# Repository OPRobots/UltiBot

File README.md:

# UltiBot

Robot de Minisumo con 6 sensores SHARP GP2Y0E03

<table>
<tr>
<td  colspan="2">  </td>
</tr>
<tr>
<td>  </td>
<td>  </td>
</tr>
</table>

## Hardware
- STM32F401CCU6 (Principal) Y STM32F103C8T6 (FOC)
- 2x SimleFOCMini
- 2x Motores gimbal 12v 80T
- 2xLiPo 3S ~180 mAh
- 6x Sensores SHARP GP2Y0E03
- 2x Sensores QRE1113
- Ruedas JSUMO JS2622
- Chasis impreso en PLA

## Software
- Programado con VSCode y PlatformIO
- Disponible programa con estrategias básicas

## KiCAD

### PCB UltiBot v1.0

### Librerías

Las librerías necesarias para este proyecto se encuentran en [OPRobots/KiCADLibraries](https://github.com/OPRobots/KiCADLibraries)

La estructura tiene que quedar de la siguiente forma:

```bash
└── kicad_project
    └── custom_libraries
        ├── custom_footprints
        │   ├── *.kicad_mod
        │   └── ...
        └── custom_symbols.kicad_sym
```

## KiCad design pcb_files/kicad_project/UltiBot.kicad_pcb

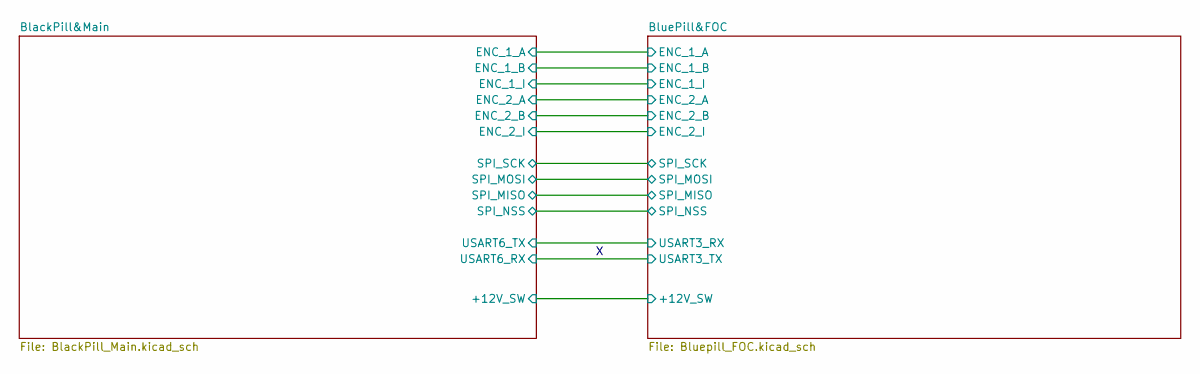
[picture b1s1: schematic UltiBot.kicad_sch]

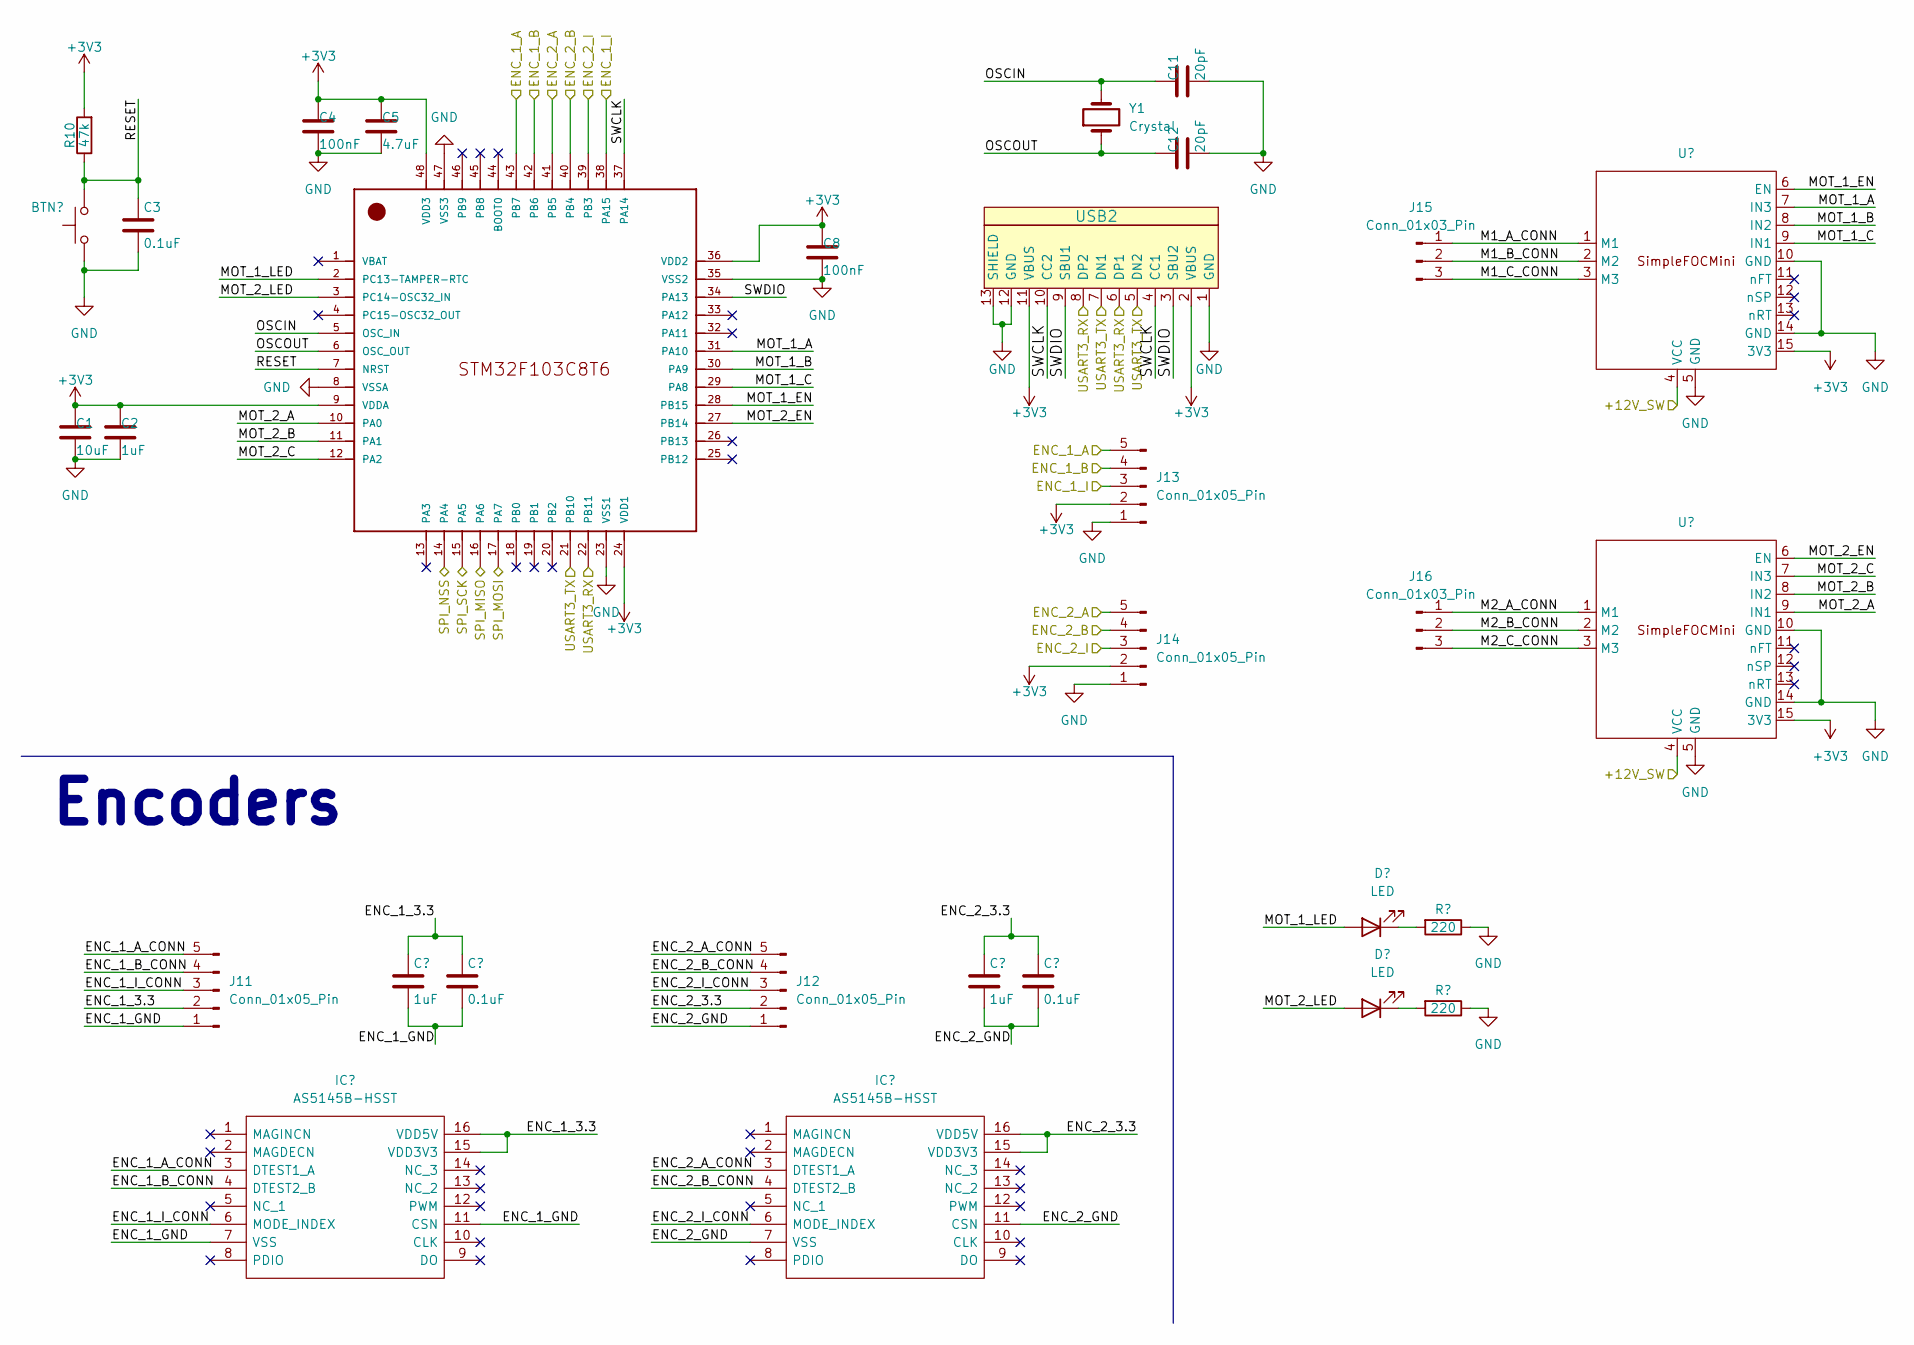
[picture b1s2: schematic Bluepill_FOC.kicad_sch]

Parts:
BTN3: SW_SPST_EVQPE1
C1: 10uF; C_0805_2012Metric
C2, C6, C9: 1uF; C_0805_2012Metric
C3, C7, C10: 0.1uF; C_0805_2012Metric
C4, C8: 100nF; C_0805_2012Metric
C5: 4.7uF; C_0805_2012Metric
C11, C12: 20pF; C_0805_2012Metric
D8, D9: LED; LED_0805_2012Metric
IC1, IC2: AS5145B-HSST; SSOP-16_5.3x6.2mm_P0.65mm
J11, J12, J13, J14: Conn_01x05_Pin; 1x05 Pad
J15, J16: Conn_01x03_Pin; PinHeader_1x03_P2.54mm_Vertical
R10: 47k; R_0805_2012Metric
R11, R12: 220; R_0805_2012Metric_Pad1.20x1.40mm_HandSolder
U2: BluePill; LQFP-48_7x7mm_P0.5mm
U3, U4: SimpleFOCMini
USB2: USB-C ST-Link USART
Y1: Crystal; Crystal_SMD_5032-2Pin_5.0x3.2mm

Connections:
+3V3: C1.1, C2.1, C4.1, C5.1, C8.1, J13.2, J14.2, R10.2, U2.9 (VDDA), U2.24 (VDD1), U2.36 (VDD2), U2.48 (VDD3), U3.15 (3V3), U4.15 (3V3), USB2.2 (VBUS), USB2.11 (VBUS); also elsewhere on the board
/BlackPill&Main/+12V_SW: U3.4 (VCC), U4.4 (VCC); also elsewhere on the board
/BlackPill&Main/ENC_1_A: J13.5, U2.43 (PB7); also elsewhere on the board
/BlackPill&Main/ENC_1_B: J13.4, U2.42 (PB6); also elsewhere on the board
/BlackPill&Main/ENC_1_I: J13.3, U2.38 (PA15); also elsewhere on the board
/BlackPill&Main/ENC_2_A: J14.5, U2.41 (PB5); also elsewhere on the board
/BlackPill&Main/ENC_2_B: J14.4, U2.40 (PB4); also elsewhere on the board
/BlackPill&Main/ENC_2_I: J14.3, U2.39 (PB3); also elsewhere on the board
/BlackPill&Main/SPI_MISO: U2.16 (PA6); also elsewhere on the board
/BlackPill&Main/SPI_MOSI: U2.17 (PA7); also elsewhere on the board
/BlackPill&Main/SPI_NSS: U2.14 (PA4); also elsewhere on the board
/BlackPill&Main/SPI_SCK: U2.15 (PA5); also elsewhere on the board
/BlackPill&Main/USART6_RX: U2.21 (PB10), USB2.5 (DN2), USB2.7 (DN1); also elsewhere on the board
/BlackPill&Main/USART6_TX: U2.22 (PB11), USB2.6 (DP1), USB2.8 (DP2); also elsewhere on the board
/BluePill&FOC/ENC_1_3.3: C6.1, C7.1, IC1.15 (VDD3V3), IC1.16 (VDD5V), J11.2
/BluePill&FOC/ENC_1_A_CONN: IC1.3 (DTEST1_A), J11.5
/BluePill&FOC/ENC_1_B_CONN: IC1.4 (DTEST2_B), J11.4
/BluePill&FOC/ENC_1_GND: C6.2, C7.2, IC1.7 (VSS), IC1.11 (CSN), J11.1
/BluePill&FOC/ENC_1_I_CONN: IC1.6 (MODE_INDEX), J11.3
/BluePill&FOC/ENC_2_3.3: C9.1, C10.1, IC2.15 (VDD3V3), IC2.16 (VDD5V), J12.2
/BluePill&FOC/ENC_2_A_CONN: IC2.3 (DTEST1_A), J12.5
/BluePill&FOC/ENC_2_B_CONN: IC2.4 (DTEST2_B), J12.4
/BluePill&FOC/ENC_2_GND: C9.2, C10.2, IC2.7 (VSS), IC2.11 (CSN), J12.1
/BluePill&FOC/ENC_2_I_CONN: IC2.6 (MODE_INDEX), J12.3
/BluePill&FOC/M1_A_CONN: J15.1, U3.1 (M1)
/BluePill&FOC/M1_B_CONN: J15.2, U3.2 (M2)
/BluePill&FOC/M1_C_CONN: J15.3, U3.3 (M3)
/BluePill&FOC/M2_A_CONN: J16.1, U4.1 (M1)
/BluePill&FOC/M2_B_CONN: J16.2, U4.2 (M2)
/BluePill&FOC/M2_C_CONN: J16.3, U4.3 (M3)
/BluePill&FOC/MOT_1_A: U2.31 (PA10), U3.7 (IN3)
/BluePill&FOC/MOT_1_B: U2.30 (PA9), U3.8 (IN2)
/BluePill&FOC/MOT_1_C: U2.29 (PA8), U3.9 (IN1)
/BluePill&FOC/MOT_1_EN: U2.28 (PB15), U3.6 (EN)
/BluePill&FOC/MOT_1_LED: D8.2 (A), U2.2 (PC13-TAMPER-RTC)
/BluePill&FOC/MOT_2_A: U2.10 (PA0), U4.9 (IN1)
/BluePill&FOC/MOT_2_B: U2.11 (PA1), U4.8 (IN2)
/BluePill&FOC/MOT_2_C: U2.12 (PA2), U4.7 (IN3)
/BluePill&FOC/MOT_2_EN: U2.27 (PB14), U4.6 (EN)
/BluePill&FOC/MOT_2_LED: D9.2 (A), U2.3 (PC14-OSC32_IN)
/BluePill&FOC/OSCIN: C11.1, U2.5 (OSC_IN), Y1.2
/BluePill&FOC/OSCOUT: C12.1, U2.6 (OSC_OUT), Y1.1
/BluePill&FOC/RESET: BTN3.2, C3.1, R10.1, U2.7 (NRST)
/BluePill&FOC/SWCLK: U2.37 (PA14), USB2.4 (CC1), USB2.10 (CC2)
/BluePill&FOC/SWDIO: U2.34 (PA13), USB2.3 (SBU2), USB2.9 (SBU1)
GND: BTN3.1, C1.2, C2.2, C3.2, C4.2, C5.2, C8.2, C11.2, C12.2, J13.1, J14.1, R11.1, R12.1, U2.8 (VSSA), U2.23 (VSS1), U2.35 (VSS2), U2.47 (VSS3), U3.5 (GND), U3.10 (GND), U3.14 (GND), U4.5 (GND), U4.10 (GND), U4.14 (GND), USB2.1 (GND), USB2.12 (GND), USB2.13 (SHIELD); also elsewhere on the board
unnamed: D8.1 (K), R11.2
unnamed: D9.1 (K), R12.2

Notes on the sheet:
Encoders

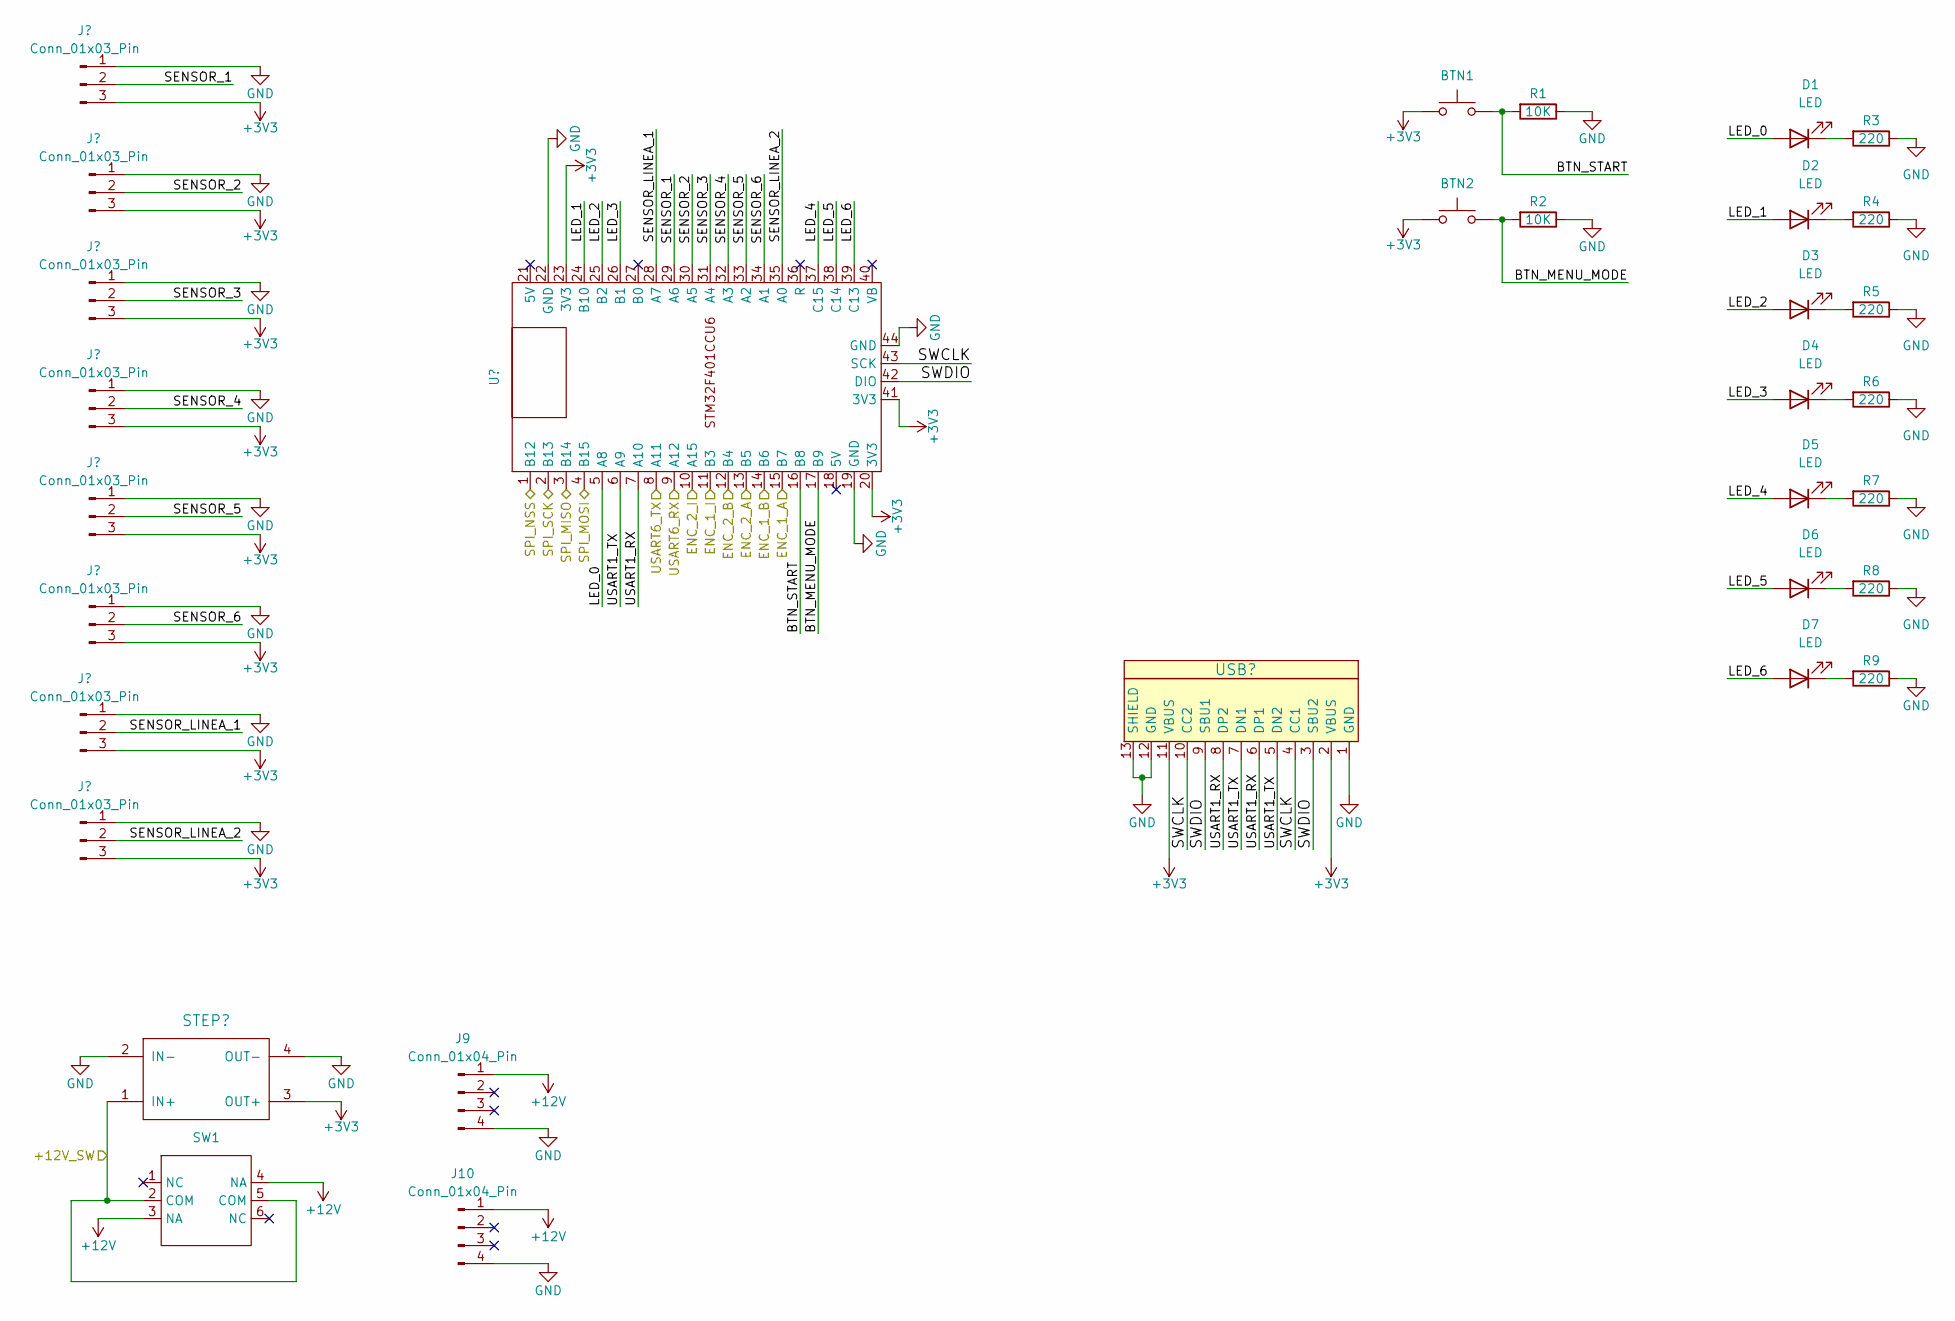
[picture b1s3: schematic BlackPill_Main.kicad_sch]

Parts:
BTN1, BTN2: SW_SPST_EVQPE1
D1, D2, D3, D4, D5, D6, D7: LED; LED_0805_2012Metric
J1, J2, J3, J4, J5, J6, J7, J8: Conn_01x03_Pin; PinHeader_1x03_P2.54mm_Vertical
J9, J10: Conn_01x04_Pin; JST_XH_B4B-XH-AM_1x04_P2.50mm_Vertical
R1, R2: 10K; R_0805_2012Metric_Pad1.20x1.40mm_HandSolder
R3, R4, R5, R6, R7, R8, R9: 220; R_0805_2012Metric_Pad1.20x1.40mm_HandSolder
STEP1: Mini360
SW1: Switch6P
U1: BlackPill_STM32F401
USB1: USB-C ST-Link USART

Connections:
+3V3: BTN1.1, BTN2.1, J1.3, J2.3, J3.3, J4.3, J5.3, J6.3, J7.3, J8.3, STEP1.3 (OUT+), U1.20 (3V3), U1.23 (3V3), U1.41 (3V3), USB1.2 (VBUS), USB1.11 (VBUS); also elsewhere on the board
+12V: J9.1, J10.1, SW1.3 (NA), SW1.4 (NA); also elsewhere on the board
/BlackPill&Main/+12V_SW: STEP1.1 (IN+), SW1.2 (COM), SW1.5 (COM); also elsewhere on the board
/BlackPill&Main/BTN_MENU_MODE: BTN2.2, R2.2, U1.17 (B9)
/BlackPill&Main/BTN_START: BTN1.2, R1.2, U1.16 (B8)
/BlackPill&Main/ENC_1_A: U1.15 (B7); also elsewhere on the board
/BlackPill&Main/ENC_1_B: U1.14 (B6); also elsewhere on the board
/BlackPill&Main/ENC_1_I: U1.11 (B3); also elsewhere on the board
/BlackPill&Main/ENC_2_A: U1.13 (B5); also elsewhere on the board
/BlackPill&Main/ENC_2_B: U1.12 (B4); also elsewhere on the board
/BlackPill&Main/ENC_2_I: U1.10 (A15); also elsewhere on the board
/BlackPill&Main/LED_0: D1.2 (A), U1.5 (A8)
/BlackPill&Main/LED_1: D2.2 (A), U1.24 (B10)
/BlackPill&Main/LED_2: D3.2 (A), U1.25 (B2)
/BlackPill&Main/LED_3: D4.2 (A), U1.26 (B1)
/BlackPill&Main/LED_4: D5.2 (A), U1.37 (C15)
/BlackPill&Main/LED_5: D6.2 (A), U1.38 (C14)
/BlackPill&Main/LED_6: D7.2 (A), U1.39 (C13)
/BlackPill&Main/SENSOR_1: J1.2, U1.29 (A6)
/BlackPill&Main/SENSOR_2: J4.2, U1.30 (A5)
/BlackPill&Main/SENSOR_3: J5.2, U1.31 (A4)
/BlackPill&Main/SENSOR_4: J6.2, U1.32 (A3)
/BlackPill&Main/SENSOR_5: J7.2, U1.33 (A2)
/BlackPill&Main/SENSOR_6: J8.2, U1.34 (A1)
/BlackPill&Main/SENSOR_LINEA_1: J2.2, U1.28 (A7)
/BlackPill&Main/SENSOR_LINEA_2: J3.2, U1.35 (A0)
/BlackPill&Main/SPI_MISO: U1.3 (B14); also elsewhere on the board
/BlackPill&Main/SPI_MOSI: U1.4 (B15); also elsewhere on the board
/BlackPill&Main/SPI_NSS: U1.1 (B12); also elsewhere on the board
/BlackPill&Main/SPI_SCK: U1.2 (B13); also elsewhere on the board
/BlackPill&Main/SWCLK: U1.43 (SCK), USB1.4 (CC1), USB1.10 (CC2)
/BlackPill&Main/SWDIO: U1.42 (DIO), USB1.3 (SBU2), USB1.9 (SBU1)
/BlackPill&Main/USART1_RX: U1.7 (A10), USB1.6 (DP1), USB1.8 (DP2)
/BlackPill&Main/USART1_TX: U1.6 (A9), USB1.5 (DN2), USB1.7 (DN1)
/BlackPill&Main/USART6_RX: U1.9 (A12); also elsewhere on the board
/BlackPill&Main/USART6_TX: U1.8 (A11); also elsewhere on the board
GND: J1.1, J2.1, J3.1, J4.1, J5.1, J6.1, J7.1, J8.1, J9.4, J10.4, R1.1, R2.1, R3.1, R4.1, R5.1, R6.1, R7.1, R8.1, R9.1, STEP1.2 (IN-), STEP1.4 (OUT-), U1.19 (GND), U1.22 (GND), U1.44 (GND), USB1.1 (GND), USB1.12 (GND), USB1.13 (SHIELD); also elsewhere on the board
unnamed: D1.1 (K), R3.2
unnamed: D2.1 (K), R4.2
unnamed: D3.1 (K), R5.2
unnamed: D4.1 (K), R6.2
unnamed: D5.1 (K), R7.2
unnamed: D6.1 (K), R8.2
unnamed: D7.1 (K), R9.2

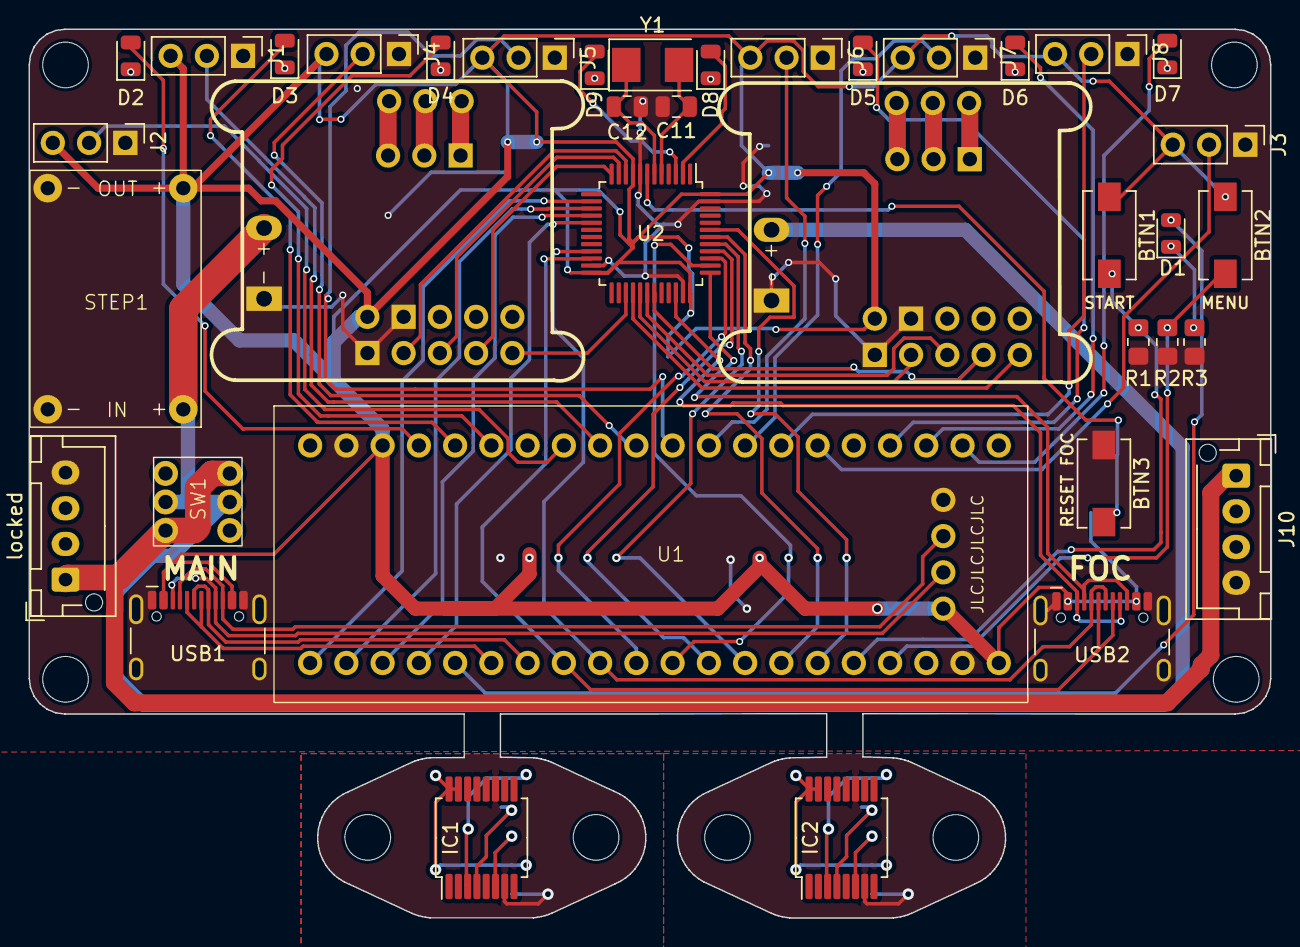
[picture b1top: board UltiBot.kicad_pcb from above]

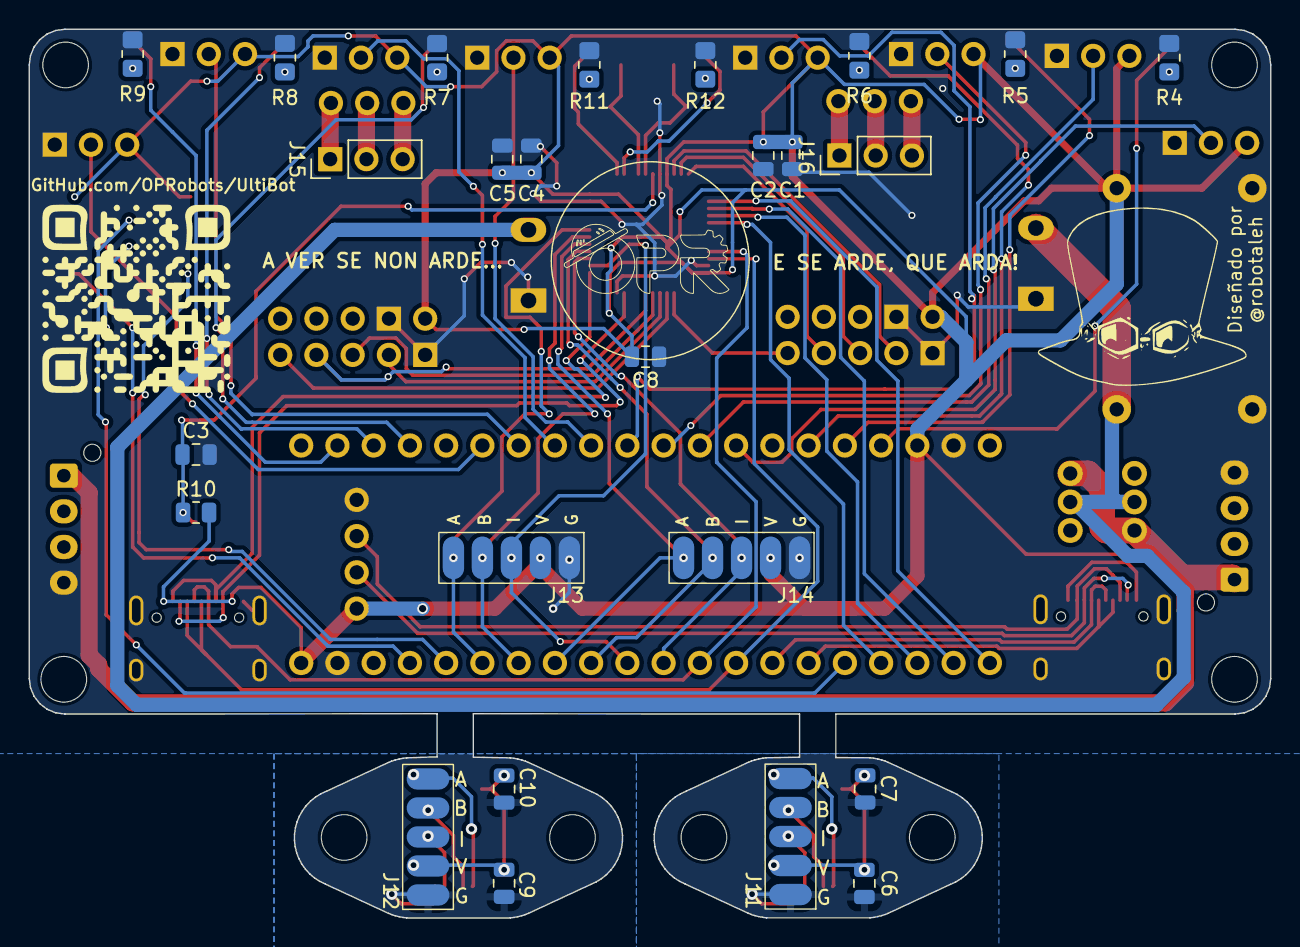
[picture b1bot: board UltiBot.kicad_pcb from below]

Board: 2 copper layers, 87.0 x 62.3 mm, 63 parts (25 on the bottom side), 77 nets.

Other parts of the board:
locked: Conn_01x04_Pin; JST_XH_B4B-XH-AM_1x04_P2.50mm_Vertical

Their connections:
+12V: locked.1; also elsewhere on the board
GND: locked.4; also elsewhere on the board

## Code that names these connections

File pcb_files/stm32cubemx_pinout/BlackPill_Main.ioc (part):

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Mcu.Name=STM32F401C(B-C)Ux
Mcu.Package=UFQFPN48
Mcu.UserName=STM32F401CCUx
PA0-WKUP.Signal=ADCx_IN0
PA1.Signal=ADCx_IN1
PA10.Mode=Asynchronous
PA10.Signal=USART1_RX
PA11.Mode=Asynchronous
PA11.Signal=USART6_TX
PA12.Mode=Asynchronous
PA12.Signal=USART6_RX
PA13.Signal=SYS_JTMS-SWDIO
PA14.Signal=SYS_JTCK-SWCLK
PA15.GPIOParameters=GPIO_Label
PA15.GPIO_Label=ENC_2_I
PA15.Signal=GPXTI15
PA2.Signal=ADCx_IN2
PA3.Signal=ADCx_IN3
PA4.Signal=ADCx_IN4
PA5.Signal=ADCx_IN5
PA6.Signal=ADCx_IN6
PA7.Signal=ADCx_IN7
PA8.GPIOParameters=GPIO_Label
PA8.GPIO_Label=LED_5
PA8.Signal=GPIO_Output
PA9.Mode=Asynchronous
PA9.Signal=USART1_TX
PB1.GPIOParameters=GPIO_Label
PB1.GPIO_Label=LED_6
PB1.Signal=GPIO_Output
PB10.GPIOParameters=GPIO_Label
PB10.GPIO_Label=LED_4
PB10.Signal=GPIO_Output
PB12.Mode=NSS_Signal_Hard_Output
PB12.Signal=SPI2_NSS
PB13.Mode=Full_Duplex_Master
PB13.Signal=SPI2_SCK
PB14.Mode=Full_Duplex_Master
PB14.Signal=SPI2_MISO
PB15.Mode=Full_Duplex_Master
PB15.Signal=SPI2_MOSI
PB2.GPIOParameters=GPIO_Label
PB2.GPIO_Label=LED_3
PB2.Signal=GPIO_Output
PB3.GPIOParameters=GPIO_Label
PB3.GPIO_Label=ENC_1_I
PB3.Signal=GPXTI3
PB4.GPIOParameters=GPIO_Label
PB4.GPIO_Label=ENC_2_B
PB4.Signal=S_TIM3_CH1
PB5.GPIOParameters=GPIO_Label
PB5.GPIO_Label=ENC_2_A
PB5.Signal=S_TIM3_CH2
PB6.GPIOParameters=GPIO_Label
PB6.GPIO_Label=ENC_1_B
PB6.Signal=S_TIM4_CH1
PB7.GPIOParameters=GPIO_Label
PB7.GPIO_Label=ENC_1_A
PB7.Signal=S_TIM4_CH2
PB8.GPIOParameters=GPIO_Label
PB8.GPIO_Label=BTN_START
PB8.Signal=GPIO_Input
PB9.GPIOParameters=GPIO_Label
PB9.GPIO_Label=BTN_MENU_MODE
PB9.Signal=GPIO_Input
PC13-ANTI_TAMP.GPIOParameters=GPIO_Label
PC13-ANTI_TAMP.GPIO_Label=LED_0
PC13-ANTI_TAMP.Signal=GPIO_Output
PC14-OSC32_IN.GPIOParameters=GPIO_Label
PC14-OSC32_IN.GPIO_Label=LED_1
PC14-OSC32_IN.Signal=GPIO_Output
PC15-OSC32_OUT.GPIOParameters=GPIO_Label
PC15-OSC32_OUT.GPIO_Label=LED_2
PC15-OSC32_OUT.Signal=GPIO_Output
PH0\ -\ OSC_IN.Signal=RCC_OSC_IN
PH1\ -\ OSC_OUT.Signal=RCC_OSC_OUT
RCC.HSE_VALUE=25000000
RCC.SYSCLKFreq_VALUE=16000000
board=custom

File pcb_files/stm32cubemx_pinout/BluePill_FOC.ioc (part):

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Mcu.Name=STM32F103C(8-B)Tx
Mcu.Package=LQFP48
Mcu.UserName=STM32F103C8Tx
PA0-WKUP.GPIOParameters=GPIO_Label
PA0-WKUP.GPIO_Label=MOT_2_A
PA0-WKUP.Signal=S_TIM2_CH1_ETR
PA1.GPIOParameters=GPIO_Label
PA1.GPIO_Label=MOT_2_B
PA1.Signal=S_TIM2_CH2
PA10.GPIOParameters=GPIO_Label
PA10.GPIO_Label=MOT_1_A
PA10.Signal=S_TIM1_CH3
PA13.Signal=SYS_JTMS-SWDIO
PA14.Signal=SYS_JTCK-SWCLK
PA15.GPIOParameters=GPIO_Label
PA15.GPIO_Label=ENC_2_I
PA15.Signal=GPXTI15
PA2.GPIOParameters=GPIO_Label
PA2.GPIO_Label=MOT_2_C
PA2.Signal=S_TIM2_CH3
PA4.Mode=NSS_Signal_Hard_Input
PA4.Signal=SPI1_NSS
PA5.Mode=Full_Duplex_Slave
PA5.Signal=SPI1_SCK
PA6.Mode=Full_Duplex_Slave
PA6.Signal=SPI1_MISO
PA7.Mode=Full_Duplex_Slave
PA7.Signal=SPI1_MOSI
PA8.GPIOParameters=GPIO_Label
PA8.GPIO_Label=MOT_1_C
PA8.Signal=S_TIM1_CH1
PA9.GPIOParameters=GPIO_Label
PA9.GPIO_Label=MOT_1_B
PA9.Signal=S_TIM1_CH2
PB10.Mode=Asynchronous
PB10.Signal=USART3_TX
PB11.Mode=Asynchronous
PB11.Signal=USART3_RX
PB14.GPIOParameters=GPIO_Label
PB14.GPIO_Label=MOT_2_EN
PB14.Signal=GPIO_Output
PB15.GPIOParameters=GPIO_Label
PB15.GPIO_Label=MOT_1_EN
PB15.Signal=GPIO_Output
PB3.GPIOParameters=GPIO_Label
PB3.GPIO_Label=ENC_1_I
PB3.Signal=GPXTI3
PB4.GPIOParameters=GPIO_Label
PB4.GPIO_Label=ENC_2_B
PB4.Signal=S_TIM3_CH1
PB5.GPIOParameters=GPIO_Label
PB5.GPIO_Label=ENC_2_A
PB5.Signal=S_TIM3_CH2
PB6.GPIOParameters=GPIO_Label
PB6.GPIO_Label=ENC_1_B
PB6.Signal=S_TIM4_CH1
PB7.GPIOParameters=GPIO_Label
PB7.GPIO_Label=ENC_1_A
PB7.Signal=S_TIM4_CH2
PC13-TAMPER-RTC.GPIOParameters=GPIO_Label
PC13-TAMPER-RTC.GPIO_Label=MOT_1_LED
PC13-TAMPER-RTC.Signal=GPIO_Output
PC14-OSC32_IN.GPIOParameters=GPIO_Label
PC14-OSC32_IN.GPIO_Label=MOT_2_LED
PC14-OSC32_IN.Signal=GPIO_Output
PD0-OSC_IN.Signal=RCC_OSC_IN
PD1-OSC_OUT.Signal=RCC_OSC_OUT
board=custom

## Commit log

2023-03-28 Añade ficheros iniciales del proyecto (modelo y código)
2023-03-28 Actualiza timings y corrige gambada del index en la funcion `set_rgb`
2023-03-28 Mejora nomenclatura de leds, ordena RGB y refactor general de comentarios sin uso
2023-03-30 Añade configuración de Timer de motores, cambia el Timer del RGB y añade gestión del botón de la placa
2023-04-01 Añade configuración USART1
2023-04-01 Añade lectura de sensores
2023-04-07 Ajusta prioridades de timers y elimina el Builtin BTN
2023-04-07 Elimina el movimiento de motores al iniciar su timer
2023-04-07 Añade funciones de leds para `rainbow` y `loading`
2023-04-07 Añade funciones básicas de botones
2023-04-07 Actualiza los files.associations del workspace
2023-04-09 Actualiza prototipo de funciones de leds para usar enum
2023-04-09 Añade obtención individual de valor de sensor raw y calibrado
2023-04-09 Añade fichero de control y funciones de competición iniciada y main loop
2023-04-11 Añade gestión de motores y funciones útiles
2023-04-12 Añade configuración del Serial a platformio.ini
2023-04-12 Actualiza índices de los sensores de rival y constantes
2023-04-12 Añade debug de sensores por RGB
2023-04-14 Actualiza diseño SketchUp
2023-04-14 Corrige lógica de botones
2023-04-14 Añade control de inicio de competición y prográma básico
2023-04-14 Añade función de leds para fatal_error
2023-04-14 Añade estructura de estrategias
2023-04-16 Añade gestión de Estados, Aperturas y Estrategias
2023-04-18 Simplifica la gestión de los motores
2023-04-18 Añade gestión de sensores inicial
2023-04-18 Actualiza gestión de motores
2023-04-18 Corrige errores de sensores y añade threshold máximo
2023-04-30 Actualiza modelo3D y README y añade programa en Arduino Nano post-corto del STM32F4
2023-04-30 Mueve el programa del STM32F4 a una carpeta independiente
2023-08-24 Añade Pinout y proyecto KiCAD de la versión FOC
2023-08-24 Actualiza diseño con los primeros cambios para FOC
2023-08-24 Añade código de Arduino pos-defunción del F4
2023-08-25 Añade pinout de BlackPill, completa esquemático y asocia footprints
2023-08-25 Actualiza estructura del proyecto (symbols, footprints) y rutas relativas
2023-08-25 Añade info para las librerías de KiCAD
2023-08-25 Elimina el directorio de custom_libraries del repo
    Las librerías se gestionarán externamente desde https://github.com/OPRobots/KiCADLibraries y se incluirán en el proyecto local
2023-08-25 Actualiza pinouts
2023-08-25 Limpia código del F4 y añade pruebas de SPI
2023-08-29 Añade pruebas de SPI
2023-08-29 Añade comunicación USART (pte. limpiar) y actualiza pinouts
2023-08-29 Actualiza el esquemático de la PCB
2023-08-29 Actualiza esquemático e inicia PCB
2023-08-31 Actualiza esquemático y finaliza ruteado de PCB
2023-09-01 Termina el diseño del esquemático y PCB
2023-09-01 Añade los Gerbers de la primera versión de la PCB
2023-09-01 Añade imágenes de la PCB y actualiza README.md
2023-09-05 Añade inicio de comunicación por UART
2023-09-05 Corrige USART6 RX<>TX en la BluePill
2023-09-05 Elimina custom_libraries
2023-09-05 Añade custom_libraries mediante submodule
2023-09-05 Elimina la variante ATmega328
2023-09-17 Acualiza Modelo 3D con PCB y chasis de prueba
2023-09-17 Añade OPRcontrolFOC como submodule
2023-09-17 Actualiza estructura de gestión de comandos, mueve los .h a includes y añade submodule de OPRcontrolFOC
2023-09-22 Actualiza diseño y añade STLs
2023-09-22 Añade platformio.ini en OPRcontrolFOC
2023-09-23 Actualiza el workspace
2023-09-23 Actualiza modelo 3D y añade STLs de rampa, apliador de rueda y espaciador
2023-09-23 Limpia referencias a SPI y actualiza gpios
2023-09-25 Añade debug de sensores por leds y corrige lectura de botones
2023-09-27 Añade configuración UART para comunicaciones simultáneas
2023-09-27 Añade funciones de control de leds
2023-09-28 Corrige cálculo de posición dinámico
2023-09-28 Comenta el método de subida DFU
2023-09-28 Corrige fallo en la asignación de velocidad negativa
2023-09-28 Añade debugs de sensores y ajusta lectura de borde
2023-09-29 Añade filtro de sensores de media móvil y debug
2023-09-29 Refactor de sensores para mejora general
2023-09-29 Añade estrategia de seguimiento mediante PID
2023-10-01 Añade menú de configuración de estrategias y debug
2023-10-01 Añade movimientos de inicio y corrige el orden de los motores
2023-10-02 Añade paso a STATE_RUNNING después de OPENING
2023-10-02 Mejora lectura de sensores y corrige bug en motores
2023-10-05 Añade aceleraciones (incremento de torque)
2023-10-06 Añade OPENINGS en arco y algoritmo SITBAN
    Sistema de
    Incremento de
    Torque
    Basado en
    Aceleraciones
    Negativas
2023-12-20 Añade FOC en Closed Loop y elimina gestión de encoders
2024-02-23 Mejora general del robot · Ajusta sensibilidad de los sensores · Mejora los openings al usar FOC Closed Loop · Ajusta las constantes del PID para la STRAT_PID · Añade decoding de señal RC5 · Añade gu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
2024-02-23 Actualiza modelo 3D, STL y librerías KiCad
2024-02-23 Actualiza README e imágenes
2024-04-04 Añade opción de arranque enviando 1 y 2 desde cualquier ADDR
2024-04-24 Añade estrategia de pasitos y cambios para GranaBOT
2024-04-24 Actualiza control de FOC (buggy)
2024-10-09 Ajusta el control de las estrategias y aperturas
2024-10-11 Añade modelo 3D y stl de la nueva versión y actualiza el submodule del FOC
2025-02-27 Añade gestión de configuraciones desde IRStart
